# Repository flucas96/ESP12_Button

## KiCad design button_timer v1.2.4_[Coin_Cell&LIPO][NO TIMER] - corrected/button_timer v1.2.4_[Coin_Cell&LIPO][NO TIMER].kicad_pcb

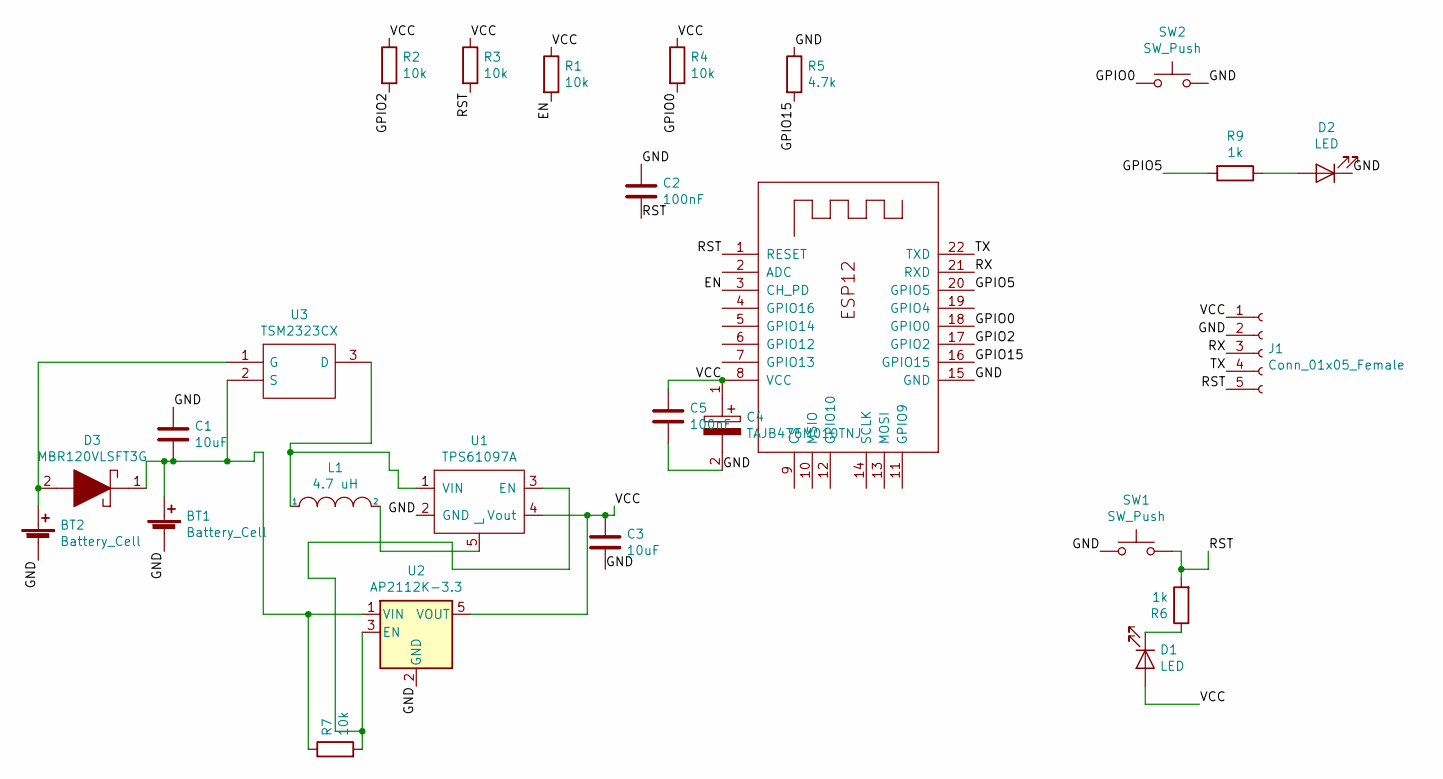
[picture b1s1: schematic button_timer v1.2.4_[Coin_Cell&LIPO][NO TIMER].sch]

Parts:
BT1: Battery_Cell; BatteryHolder_Keystone_1058_1x2032
BT2: Battery_Cell; JST_PH_B2B-PH-K_1x02_P2.00mm_Vertical
C1, C3: 10uF; C_0805_2012handsodermod
C2: 100nF; C_0805_2012handsodermod
C4: TAJB476M010TNJ; CAPPM3528X210N; Manufacturer_Part_Number TAJB476M010TNJ; Mouser Part Number 581-TAJB476M010TNJ
C5: 100nF; C_0402_1005Metric_Pad0.74x0.62mm_HandSoldermod
D1: LED; LED_1206_3216Metric_Castellated
D2: LED; LED_0805_2012Metric_Castellated_mod
D3: MBR120VLSFT3G; D_SOD-123handsoldermod; Manufacturer_Part_Number MBR120VLSFT3G; Mouser Part Number 863-MBR120VLSFT3G
J1: Conn_01x05_Female; PinSocket_1x05_P2.54mm_Vertical_mod
L1: 4.7 uH; SMD-1210_Pol_inductor
R1, R2, R3, R4, R7: 10k; R_0805_2012handsoldermod
R5: 4.7k; R_0805_2012handsoldermod
R6, R9: 1k; R_0805_2012handsoldermod
SW1: SW_Push; SW_PUSH_6mm_H8mm_mod
SW2: SW_Push; SW_SPST_B3U-1000P_mod
U1: TPS61097A; SOT-23-5_HandSolderingmod
U2: AP2112K-3.3; SOT-23-5_HandSolderingmod
U3: TSM2323CX; SOT-23; Manufacturer_Part_Number TSM2323CX; Mouser Part Number 821-TSM2323CX
X1: ESP-12E; ESP-12Elesssilk

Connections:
/EN: R1.2, X1.3 (CH_PD)
/GND: BT1.2 (-), BT2.2 (-), C1.1, C2.1, C3.2, C4.2, C5.2, D2.1 (K), J1.2, R5.1, SW1.1, SW2.2, U1.2 (GND), U2.2 (GND), X1.15 (GND)
/GPIO0: R4.2, SW2.1, X1.18 (GPIO0)
/GPIO2: R2.2, X1.17 (GPIO2)
/GPIO5: R9.2, X1.20 (GPIO5)
/GPIO15: R5.2, X1.16 (GPIO15)
/RST: C2.2, J1.5, R3.2, R6.2, SW1.2, X1.1 (RESET)
/RX: J1.3, X1.21 (RXD)
/TX: J1.4, X1.22 (TXD)
/VCC: C3.1, C4.1, C5.1, D1.2 (A), J1.1, R1.1, R2.1, R3.1, R4.1, U1.4 (Vout), U2.5 (VOUT), X1.8 (VCC)
unnamed: BT1.1 (+), C1.2, D3.1, R7.1, U2.1 (VIN), U3.2 (S)
unnamed: BT2.1 (+), D3.2, U3.1 (G)
unnamed: D1.1 (K), R6.1
unnamed: D2.2 (A), R9.1
unnamed: L1.1, U1.1 (VIN), U3.3 (D)
unnamed: L1.2, U1.5 (L)
unnamed: R7.2, U1.3 (EN), U2.3 (EN)

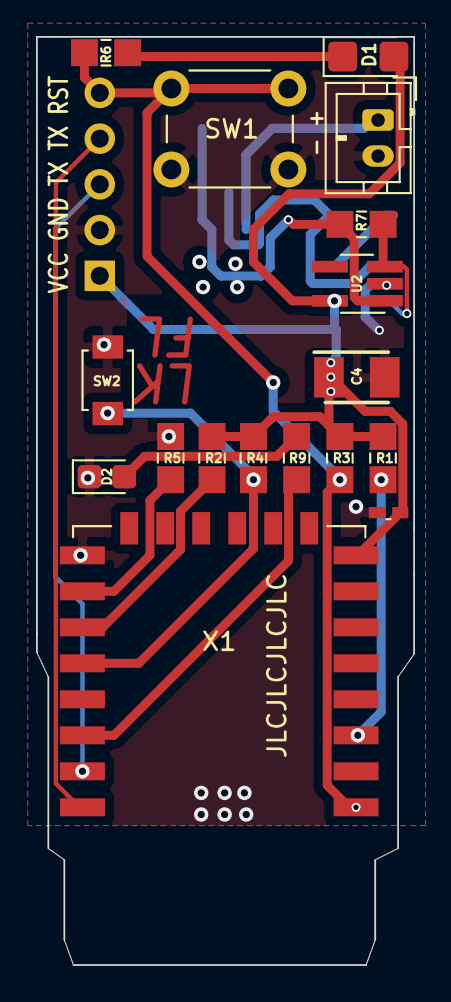
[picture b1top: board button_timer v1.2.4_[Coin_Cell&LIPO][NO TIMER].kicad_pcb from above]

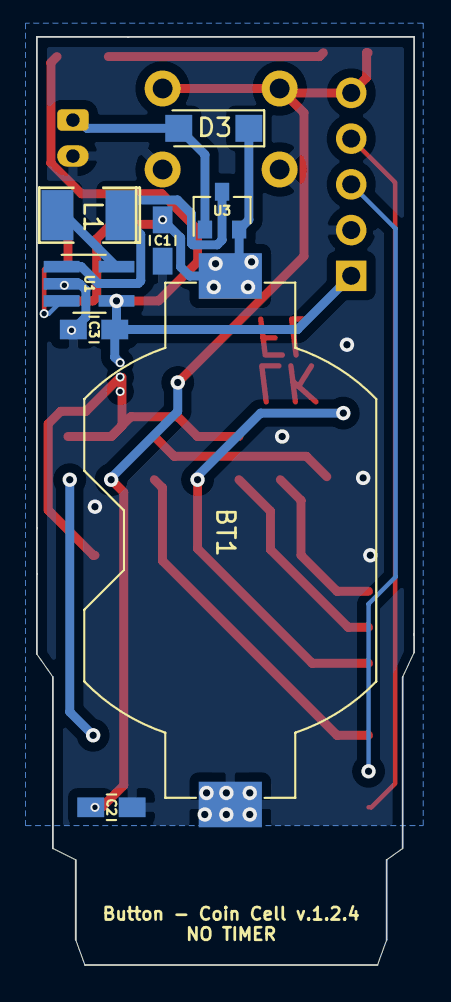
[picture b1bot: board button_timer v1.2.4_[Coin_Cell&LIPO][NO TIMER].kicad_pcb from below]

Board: 2 copper layers, 21.0 x 51.6 mm, 26 parts (8 on the bottom side), 17 nets.

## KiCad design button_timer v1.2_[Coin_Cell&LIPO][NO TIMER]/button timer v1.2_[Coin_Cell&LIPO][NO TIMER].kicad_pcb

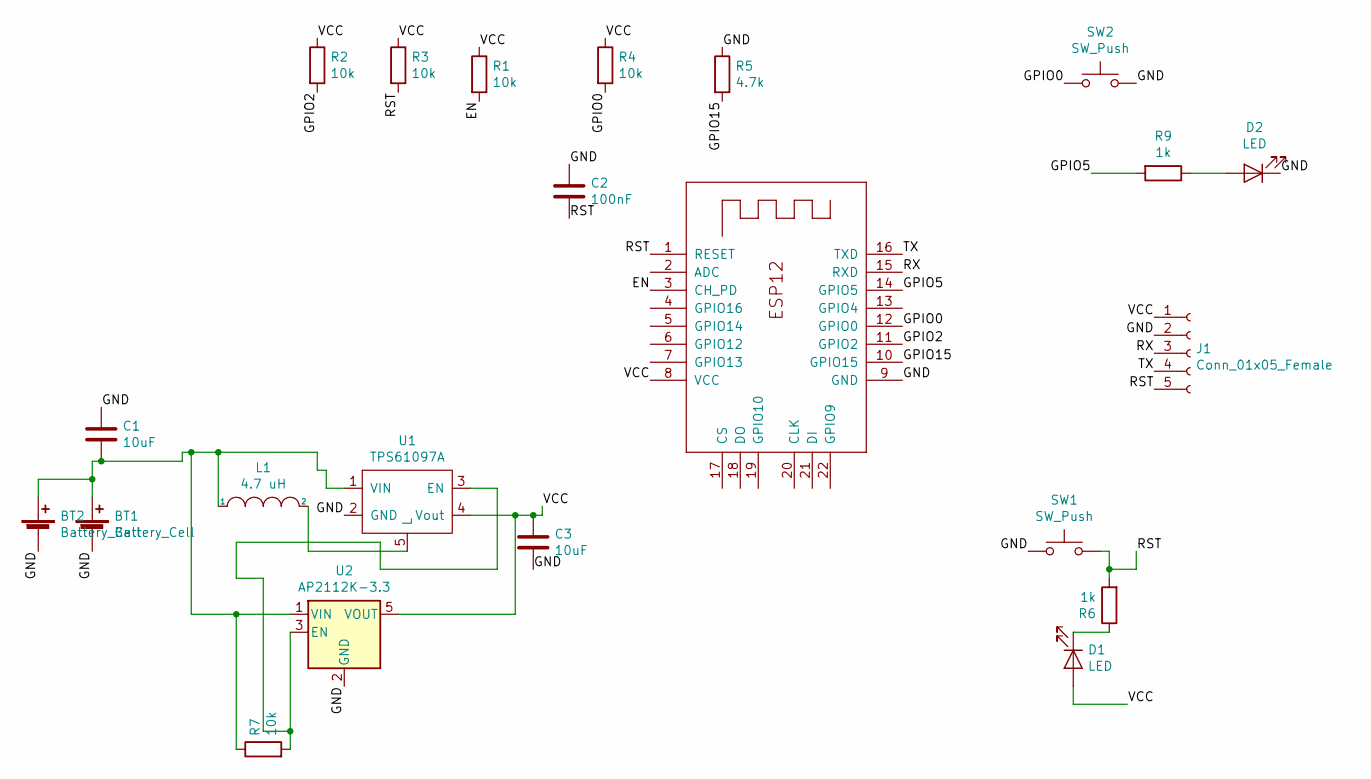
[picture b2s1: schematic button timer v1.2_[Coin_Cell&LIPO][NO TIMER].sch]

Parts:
BT1: Battery_Cell; BatteryHolder_Keystone_1058_1x2032
BT2: Battery_Cell; JST_PH_B2B-PH-K_1x02_P2.00mm_Vertical
C1, C3: 10uF; C_0805_2012handsodermod
C2: 100nF; C_0805_2012handsodermod
D1: LED; LED_1206_3216Metric_Castellated
D2: LED; LED_0805_2012Metric_Castellated
J1: Conn_01x05_Female; PinSocket_1x05_P2.54mm_Vertical_mod
L1: 4.7 uH; SMD-1210_Pol_inductor
R1, R2, R3, R4, R7: 10k; R_0805_2012handsoldermod
R5: 4.7k; R_0805_2012handsoldermod
R6, R9: 1k; R_0805_2012handsoldermod
SW1: SW_Push; SW_PUSH_6mm_H8mm_mod
SW2: SW_Push; SW_SPST_B3U-1000P_mod
U1: TPS61097A; SOT-23-5_HandSolderingmod
U2: AP2112K-3.3; SOT-23-5_HandSolderingmod
X1: ESP-12E; ESP-12Elesssilk

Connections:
/EN: R1.2, X1.3 (CH_PD)
/GND: BT1.2 (-), BT2.2 (-), C1.1, C2.1, C3.2, D2.1 (K), J1.2, R5.1, SW1.1, SW2.2, U1.2 (GND), U2.2 (GND), X1.9 (GND)
/GPIO0: R4.2, SW2.1, X1.12 (GPIO0)
/GPIO2: R2.2, X1.11 (GPIO2)
/GPIO5: R9.2, X1.14 (GPIO5)
/GPIO15: R5.2, X1.10 (GPIO15)
/RST: C2.2, J1.5, R3.2, R6.2, SW1.2, X1.1 (RESET)
/RX: J1.3, X1.15 (RXD)
/TX: J1.4, X1.16 (TXD)
/VCC: C3.1, D1.2 (A), J1.1, R1.1, R2.1, R3.1, R4.1, U1.4 (Vout), U2.5 (VOUT), X1.8 (VCC)
unnamed: BT1.1 (+), BT2.1 (+), C1.2, L1.1, R7.1, U1.1 (VIN), U2.1 (VIN)
unnamed: D1.1 (K), R6.1
unnamed: D2.2 (A), R9.1
unnamed: L1.2, U1.5 (L)
unnamed: R7.2, U1.3 (EN), U2.3 (EN)

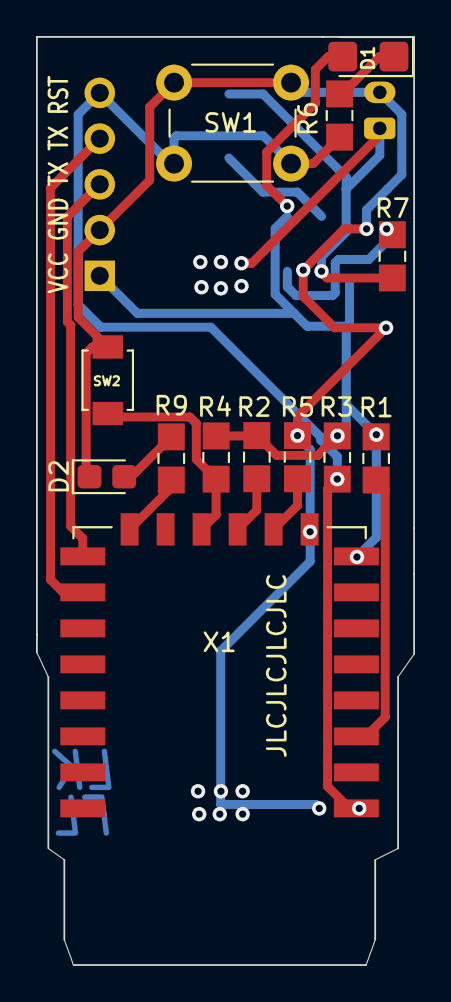
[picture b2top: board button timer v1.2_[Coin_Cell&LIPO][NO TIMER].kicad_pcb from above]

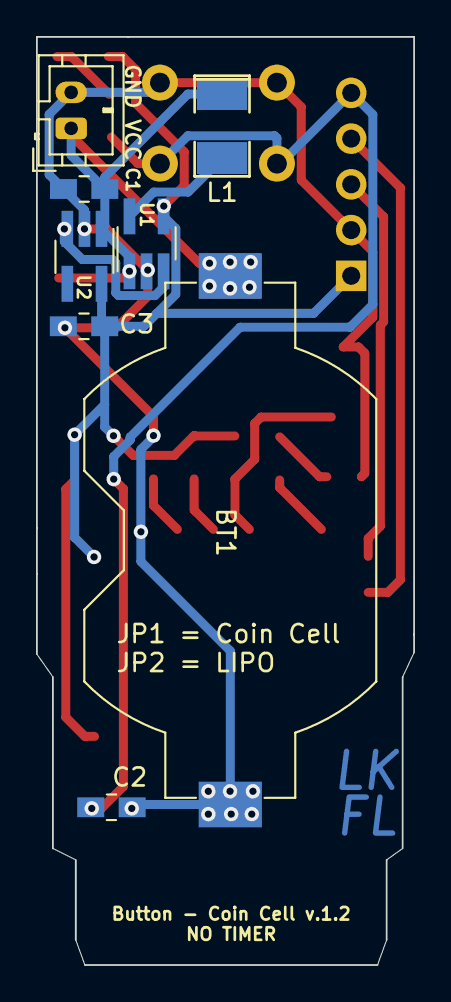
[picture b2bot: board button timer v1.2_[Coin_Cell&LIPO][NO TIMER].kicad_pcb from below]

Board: 2 copper layers, 21.0 x 51.6 mm, 22 parts (8 on the bottom side), 15 nets.
